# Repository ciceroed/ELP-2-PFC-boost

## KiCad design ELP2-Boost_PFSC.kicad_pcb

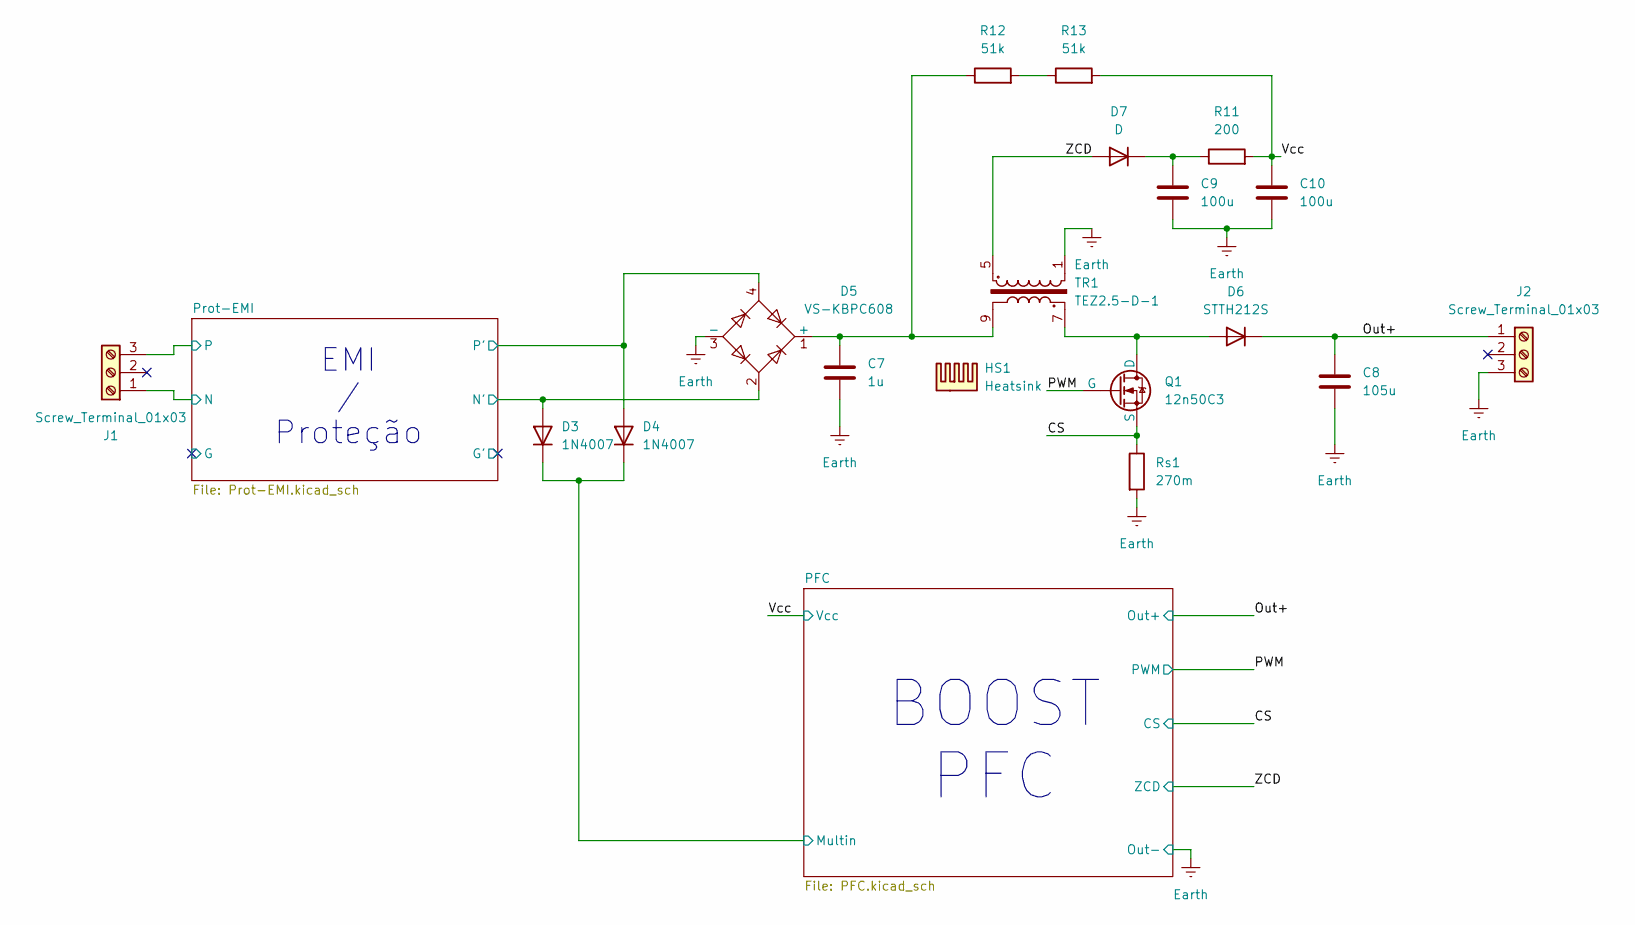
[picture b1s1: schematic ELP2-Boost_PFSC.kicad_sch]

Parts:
C7: 1u; C_Rect_L31.5mm_W9.0mm_P27.50mm_MKS4
C8: 105u; CP_Radial_D22.0mm_P10.00mm_SnapIn
C9, C10: 100u; C_Radial_D8.0mm_H11.5mm_P3.50mm
D3, D4: 1N4007; D_DO-41_SOD81_P10.16mm_Horizontal
D5: VS-KBPC608; Diode_Bridge_Vishay_KBPC6
D6: STTH212S; D_SMC-RM10_Universal_Handsoldering
D7: D; D_DO-41_SOD81_P10.16mm_Horizontal
HS1: Heatsink; Heatsink_Fischer_SK129-STS_42x25mm_2xDrill2.5mm
J1, J2: Screw_Terminal_01x03; TerminalBlock_Altech_AK300-3_P5.00mm
Q1: 12n50C3; TO-220-3_Vertical
R11: 200; R_Axial_DIN0207_L6.3mm_D2.5mm_P10.16mm_Horizontal
R12, R13: 51k; R_Axial_DIN0207_L6.3mm_D2.5mm_P10.16mm_Horizontal
Rs1: 270m; R_2512_6332Metric_Pad1.40x3.35mm_HandSolder
TR1: TEZ2.5-D-1; Indutor ELP

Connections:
/CS: Q1.3 (S), Rs1.1; also elsewhere on the board
/Out+: C8.1, D6.1 (K), J2.1; also elsewhere on the board
/PFC/Multin: D3.1 (K), D4.1 (K); also elsewhere on the board
/PWM: Q1.1 (G); also elsewhere on the board
/Prot-EMI/N: J1.1; also elsewhere on the board
/Prot-EMI/N': D3.2 (A), D5.2; also elsewhere on the board
/Prot-EMI/P: J1.3; also elsewhere on the board
/Prot-EMI/P': D4.2 (A), D5.4; also elsewhere on the board
/Vcc: C10.1, R11.2, R13.2; also elsewhere on the board
/ZCD: D7.2 (A), TR1.5; also elsewhere on the board
Earth: C7.2, C8.2, C9.2, C10.2, D5.3 (-), J2.3, Rs1.2, TR1.1; also elsewhere on the board
unnamed: C7.1, D5.1 (+), R12.1, TR1.9
unnamed: D6.2 (A), Q1.2 (D), TR1.7
unnamed: C9.1, D7.1 (K), R11.1
unnamed: R12.2, R13.1

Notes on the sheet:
EMI / Proteção
BOOST PFC

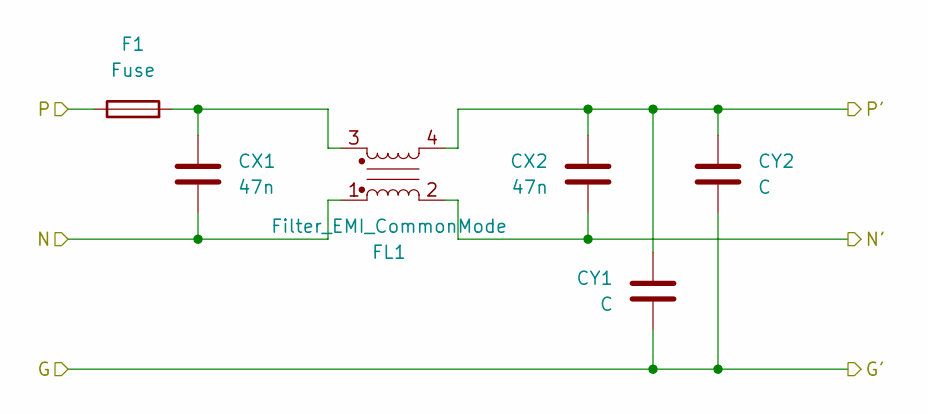
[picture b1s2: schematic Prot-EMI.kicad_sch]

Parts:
CX1, CX2: 47n; C_Rect_L24.0mm_W8.6mm_P22.50mm_MKT
CY1, CY2: C
F1: Fuse; R_Axial_DIN0207_L6.3mm_D2.5mm_P15.24mm_Horizontal
FL1: Filter_EMI_CommonMode; Filtro_EMI-Choke

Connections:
/Prot-EMI/N: CX1.2, FL1.1; also elsewhere on the board
/Prot-EMI/N': CX2.2, FL1.2; also elsewhere on the board
/Prot-EMI/P: F1.1; also elsewhere on the board
/Prot-EMI/P': CX2.1, CY1.1, CY2.1, FL1.4; also elsewhere on the board
unnamed: CX1.1, F1.2, FL1.3
unnamed: CY1.2, CY2.2

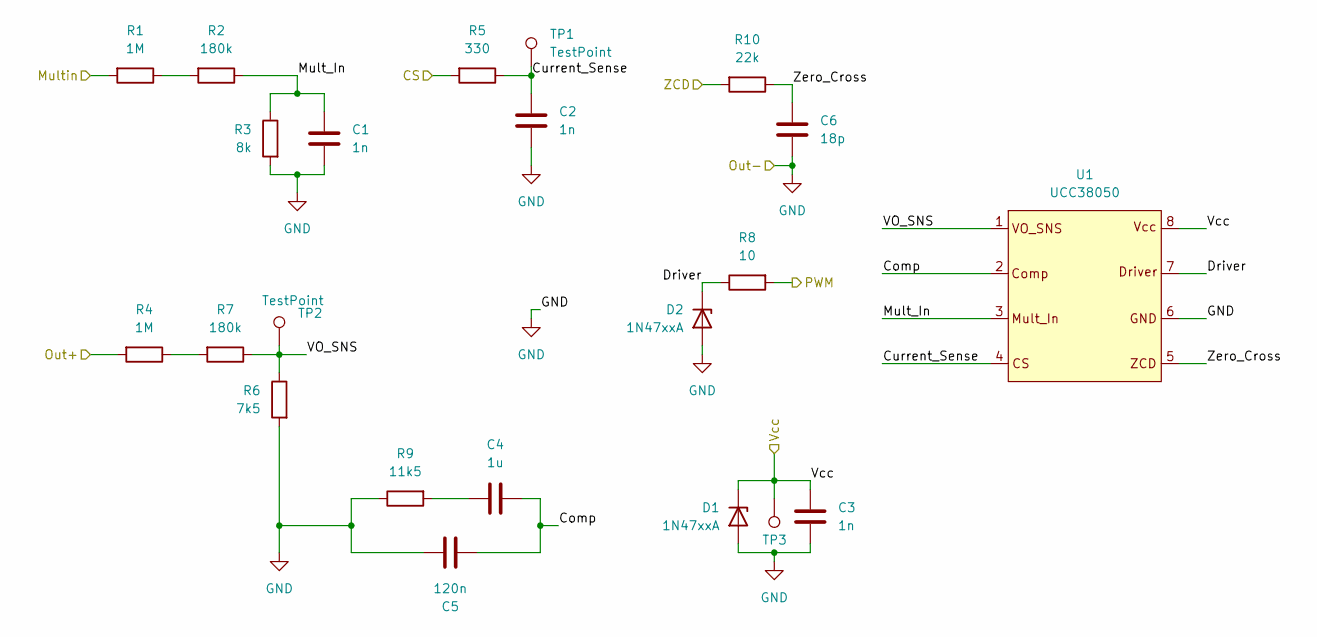
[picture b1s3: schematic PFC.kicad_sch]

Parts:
C1, C2, C3: 1n; C_Disc_D5.0mm_W2.5mm_P5.00mm
C4: 1u; C_Disc_D5.0mm_W2.5mm_P5.00mm
C5: 120n; C_Disc_D5.0mm_W2.5mm_P5.00mm
C6: 18p; C_Disc_D5.0mm_W2.5mm_P5.00mm
D1, D2: 1N47xxA; D_DO-41_SOD81_P10.16mm_Horizontal
R1, R4: 1M; R_Axial_DIN0207_L6.3mm_D2.5mm_P10.16mm_Horizontal
R2, R7: 180k; R_Axial_DIN0207_L6.3mm_D2.5mm_P10.16mm_Horizontal
R3: 8k; R_Axial_DIN0207_L6.3mm_D2.5mm_P10.16mm_Horizontal
R5: 330; R_Axial_DIN0207_L6.3mm_D2.5mm_P10.16mm_Horizontal
R6: 7k5; R_Axial_DIN0207_L6.3mm_D2.5mm_P10.16mm_Horizontal
R8: 10; R_Axial_DIN0207_L6.3mm_D2.5mm_P10.16mm_Horizontal
R9: 11k5; R_Axial_DIN0207_L6.3mm_D2.5mm_P10.16mm_Horizontal
R10: 22k; R_Axial_DIN0207_L6.3mm_D2.5mm_P10.16mm_Horizontal
TP1, TP2, TP3: TestPoint; TestPoint_THTPad_2.5x2.5mm_Drill1.2mm
U1: UCC38050; SOIC-8_3.9x4.9mm_P1.27mm

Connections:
/CS: R5.2; also elsewhere on the board
/Out+: R4.2; also elsewhere on the board
/PFC/Comp: C4.1, C5.1, U1.2
/PFC/Current_Sense: C2.1, R5.1, TP1.1, U1.4
/PFC/Driver: D2.1 (K), R8.1, U1.7
/PFC/Mult_In: C1.1, R2.1, R3.1, U1.3
/PFC/Multin: R1.2; also elsewhere on the board
/PFC/VO_SNS: R6.1, R7.1, TP2.1, U1.1
/PFC/Zero_Cross: C6.1, R10.1, U1.5
/PWM: R8.2; also elsewhere on the board
/Vcc: C3.1, D1.1 (K), TP3.1, U1.8; also elsewhere on the board
/ZCD: R10.2; also elsewhere on the board
Earth: C1.2, C2.2, C3.2, C5.2, C6.2, D1.2 (A), D2.2 (A), R3.2, R6.2, R9.1, U1.6; also elsewhere on the board
unnamed: C4.2, R9.2
unnamed: R1.1, R2.2
unnamed: R4.1, R7.2

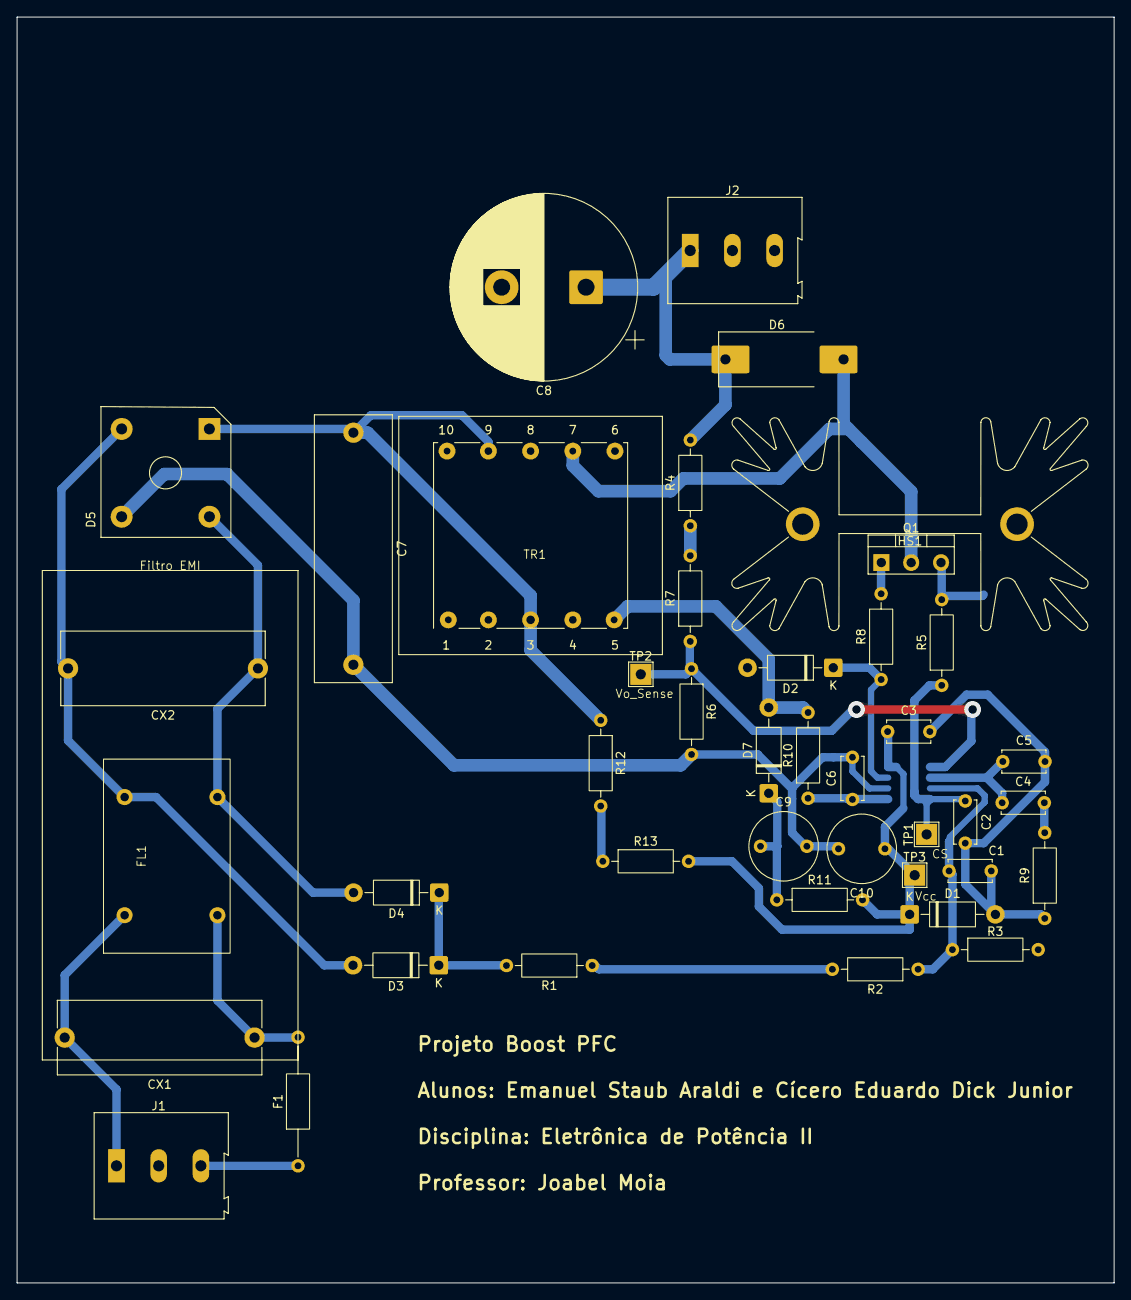
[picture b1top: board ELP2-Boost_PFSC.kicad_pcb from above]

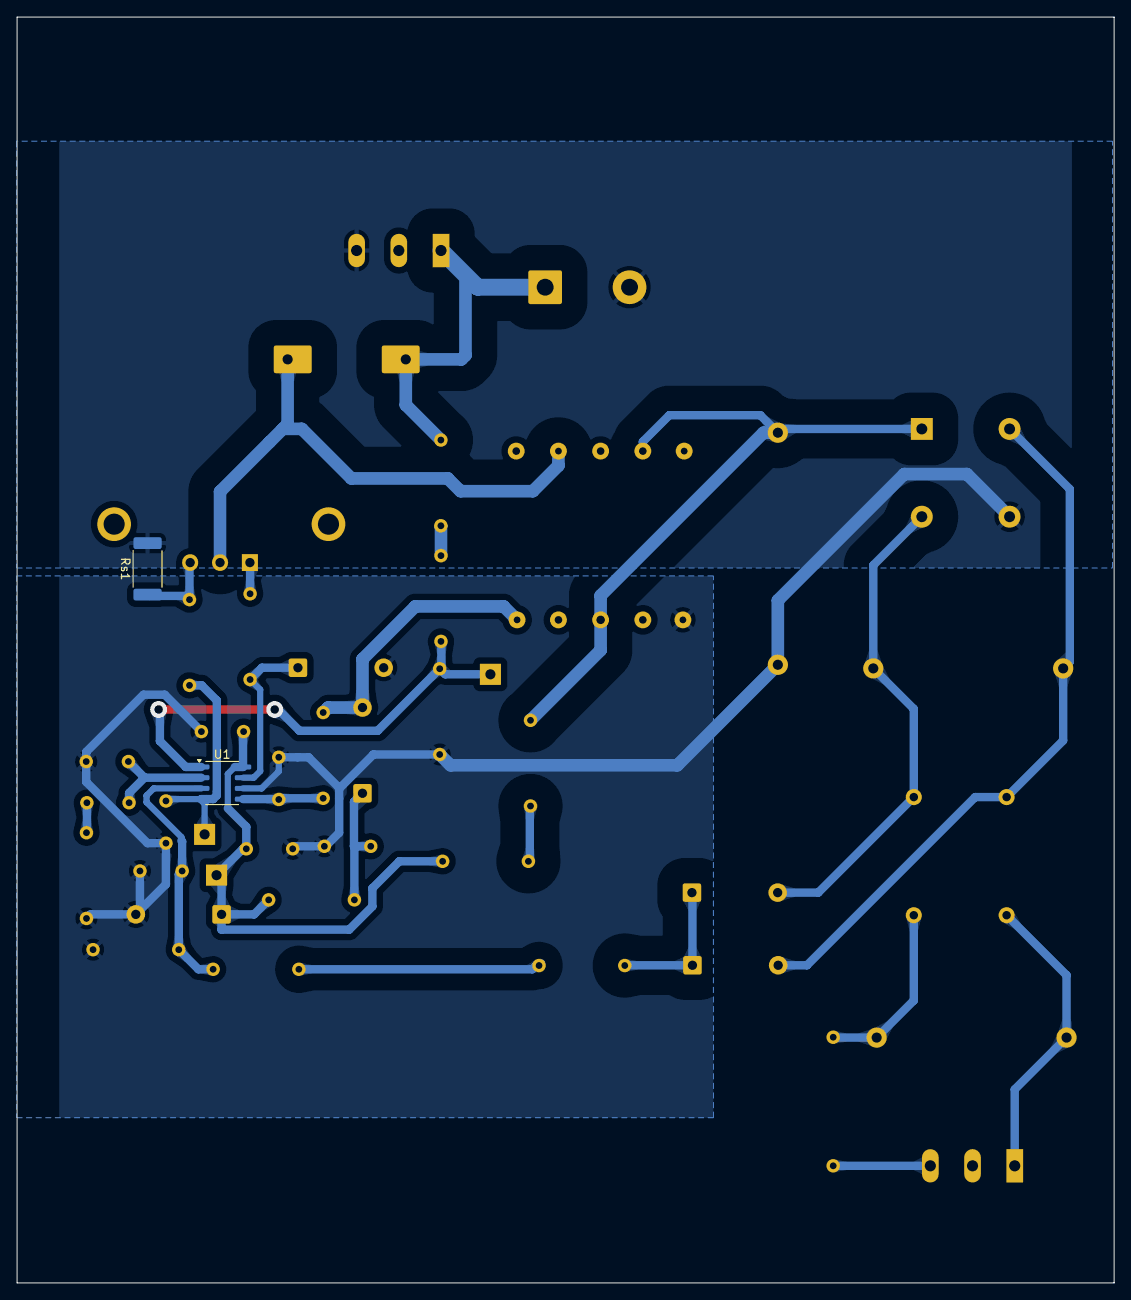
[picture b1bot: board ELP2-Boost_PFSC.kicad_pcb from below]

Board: 2 copper layers, 130.0 x 150.0 mm, 44 parts (2 on the bottom side), 25 nets.

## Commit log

2025-11-17 primeiro commit
2025-11-19 Changes: - Added netclasses - Better footprint for testpoints - EMI filter
    TODO:
    - Route the rest of the board
    - Different versions of the board to make sure its approved on monday
    - Get shunt footprint
    - Figure out wich connections can be jumpered
2025-11-20 Changes: - Grouped blocks of components for labeling/testing - Labeled Test conditions on board Todo: - Arange blocks into a more sensible shape - Connect them
2025-11-23 Changed: - Added basic routing/positioning - Better netclasses - Determined location for the IC TODO: - Finish routing - Add jumpers for voltage signals
2025-11-23 Changes: - Connected everything TODO: - Redesign so that UCC is surrounded by the ground plane
2025-11-23 Changes: - Added ground plane for analog components - Better EMI shielding on UCC and MOSFET TODO: - Try and get everything closer, somehow
2025-11-24 Placa refeita de acordo com pedidos do professor, sujeita a alteração
2025-11-27 Ajustes nos planos de referência e posição do shunt
2025-11-27 Small improvement to insulation
2025-11-27 Got all the blocks a lot closer and named the testpoints on the silkscreen
